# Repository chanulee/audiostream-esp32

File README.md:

# audiostream-esp32 — LOVELACE

AUX 스피커(3.5mm 라인 입력)에 꽂는 무선 오디오 수신기입니다. 한 개의 ESP32로 **AirPlay 2 · Spotify Connect · Bluetooth A2DP**를 모두 받고, 마지막으로 재생을 요청한 휴대폰이 출력을 가져갑니다.

| 항목 | 내용 |
|---|---|
| MCU | ESP32-WROVER-E-N8R8 (Flash 8MB, PSRAM 8MB, Wi-Fi + Bluetooth Classic) |
| DAC | PCM5102A, 3.5mm stereo line-out (2.1 Vrms) |
| 전원 | USB-C 5V → eFuse(OVP 5.8V, 전류 제한) → 3.3V buck / 저잡음 아날로그 LDO. 전원 스위치 없이 꽂으면 켜짐 |
| 보드 | LOVELACE / AS-008 rev A, 37 × 41mm 4층. USB-C와 AUX가 같은 변, 버튼 1개 |
| 수신 | AirPlay 2 (AAC/ALAC), Spotify Connect (cspot, Ogg Vorbis 320kbps), Bluetooth A2DP SBC + AVRCP |

S3 기반 이전 시제품(AS-001)은 Bluetooth Classic이 없어 A2DP를 받을 수 없으므로 WROVER로 전환했습니다. 첫 시제품부터 현재까지의 기록은 [hardware/archive](hardware/archive/README.md)에 있습니다.

## 빌드와 플래시

빌드용 Python은 3.11을 사용합니다. ESP-IDF 일부 의존성이 Python 3.14와 호환되지 않습니다.

```sh
python3.11 -m venv .venv
.venv/bin/pip install platformio==6.2.0
export PLATFORMIO_CORE_DIR="$PWD/work/platformio"
.venv/bin/pio run -d firmware -e lovelace-as-004 -t upload
.venv/bin/pio run -d firmware -e lovelace-as-004 -t uploadfs
.venv/bin/pio device monitor -b 115200
```

AS-003 이후 보드의 CH340N에는 DTR이 없어 자동 다운로드 모드 진입을 지원하지 않습니다. 업로드 전에 **버튼을 누른 채 USB를 꽂으세요.** 이후 펌웨어 업데이트는 웹 UI의 OTA로도 가능합니다.

버튼: 짧게 = 재생/일시정지, 두 번 = 다음 곡, 3초 = Bluetooth 페어링(연결된 폰을 끊고 새 폰 연결 대기).

| 환경 | 용도 |
|---|---|
| `lovelace-as-004` | 기본 펌웨어. AirPlay + Spotify + Bluetooth |
| `lovelace-as-004-capture` | 위 기능 + PCM 캡처 API (개발용, PSRAM 사용) |

## 첫 설정

1. 첫 부팅 시 `LOVELACE-Setup` Wi-Fi에 연결하고 `http://192.168.4.1/`에서 집의 2.4GHz Wi-Fi를 설정합니다.
2. Spotify: `http://<보드 IP>/spotify`에서 본인의 개발자 앱 Client ID / Secret을 입력하고 재부팅합니다. Premium 계정이 필요합니다. [설정 및 통합 설명](docs/SPOTIFY.md).
3. Bluetooth: 휴대폰의 Bluetooth 목록에서 `LOVELACE`를 선택합니다. 화면이 없으므로 Just Works 페어링을 사용하며, 구형 기기는 PIN `0000`을 사용합니다.

게스트 네트워크의 기기 격리나 mDNS 차단은 AirPlay·Spotify 검색을 방해합니다.

## 소스 전환 규칙

- 출력은 한 번에 하나의 소스만 사용합니다. 하나의 재생 태스크가 I2S를 쓰고, 소스는 `audio_source.c`의 출력 잠금 아래에서만 바뀝니다.
- **명시적 재생 요청이 출력을 가져옵니다.** AirPlay 재생, Spotify 재생/재개, Bluetooth AVRCP "playing" 보고가 해당합니다. 이전 소스는 일시정지 요청(Spotify yield, AVRCP pause)을 받고 대기 PCM은 버립니다.
- 다른 소스가 출력 중일 때 휴대폰 알림음이나 키보드 클릭처럼 A2DP 스트림만 열린 경우에는 출력을 가져오지 않습니다. 1.5초 이상 소리가 이어질 때만 재생으로 판단합니다.
- Bluetooth가 연결되어 있어도 AirPlay와 Spotify는 계속 검색됩니다. A2DP 48kHz 스트림은 I2S 클럭을 바꿔 리샘플링 없이 출력합니다.

## 테스트

```sh
sh tools/test_host.sh
```

호스트 테스트는 출력 소유권 전환(AirPlay/Spotify/Bluetooth), PCM FIFO 경계, 캡처 및 44.1/48kHz 전환, Spotify 연결 폼 파싱, WAV 저장을 확인합니다.

**검증 상태 (2026-10-16):** `lovelace-as-004` 펌웨어 0.3.1 빌드 성공, 호스트 테스트와 실크 편집기 테스트 전체 통과. **실기기 검증은 아직 없습니다.** 특히 Wi-Fi + Bluetooth + Spotify TLS를 동시에 켠 상태의 내부 RAM 여유, Wi-Fi/BT 공존 시의 끊김, 실제 계정의 Spotify 재생은 보드에서 측정해야 합니다.

### 캡처로 음질 확인

`lovelace-as-004-capture` 펌웨어에서 DAC 없이도 출력 PCM을 WAV로 받을 수 있습니다.

```sh
python3 tools/capture.py http://192.168.1.42 --seconds 3 -o capture.wav
```

[캡처 API](docs/CAPTURE_API.md)는 인증 없이 동작하므로 신뢰하는 로컬 네트워크에서만 사용하세요.

## 하드웨어

[LOVELACE / AS-008 rev A](hardware/lovelace-as-008/README.md)는 KiCad 10으로 스크립트 생성하며, [pcb-layout-skill](https://github.com/studio-edul/pcb-layout-skill)의 배치 검사기·계산기로 검증합니다. 제작 전 남은 항목은 [REVIEW.md](hardware/lovelace-as-008/REVIEW.md), 주문과 첫 보드 확인은 [BRINGUP.md](hardware/lovelace-as-008/BRINGUP.md)에 있습니다.

## 버전

| | 위치 | 버전 |
|---|---|---|
| 하드웨어 (현재) | `hardware/lovelace-as-008/` | AS-008 rev A (`plan_pcb.py`의 `BOARD_ID`, `BOARD_REV`) |
| 하드웨어 (이전) | `hardware/archive/NN-*/` | S3 rev A → AS-001 → AS-002 rev B → AS-002 rev C ([기록](hardware/archive/README.md)) |
| 펌웨어 | `firmware/version.txt` | 0.3.0 |

펌웨어 0.3.x는 AS-003부터 AS-008까지 전용입니다(AS-003–AS-006은 넷리스트가 같고, AS-007은 AUX 잭 단자 배정, AS-008은 USB via 크기와 eFuse ITIMER 미실장 패드만 다릅니다. 펌웨어와 무관합니다). 빌드 환경 이름은 `lovelace-as-004` 그대로 씁니다. DAC 뮤트(XSMT)를 GPIO22로 풀어야 소리가 나며, 0.2.x(ESP32-S3 / AS-001)는 이 보드들에서 동작하지 않습니다. 하드웨어 버전 규칙은 [archive/README.md](hardware/archive/README.md)에 있습니다.

## 문서

- [Spotify Connect 통합](docs/SPOTIFY.md)
- [연결 기능 조사: SDK, 다중 휴대폰, Bluetooth, Flash](docs/CONNECT_RESEARCH.md)
- [PCM 캡처 API](docs/CAPTURE_API.md)
- [기반 코드와 라이선스](docs/UPSTREAM.md). AirPlay 기반 코드는 비상업적 라이선스, cspot은 GPLv3입니다. 배포·판매 전에 권리 관계를 정리해야 합니다.

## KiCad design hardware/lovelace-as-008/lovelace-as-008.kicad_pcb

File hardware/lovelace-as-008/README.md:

# LOVELACE / AS-008 rev A

ESP32-WROVER-E-N8R8 + PCM5102A 일체형 수신 보드. **37 × 41 mm, 4층**, 단면 실장(JLCPCB Economic PCBA 가능). USB-C 전원과 3.5mm AUX가 아래 변에 있고, 모듈 안테나는 위 변 밖으로 나갑니다. 전원 스위치 없이 USB를 꽂으면 켜집니다.

렌더 전체(PCBA, 맨 기판, 부품 배치도, 층별 배선, 이전 빌드와의 차이, 버전 기록)는 `renders/latest/index.html`에 있습니다. 이전 버전은 [archive](../archive/README.md)에 있습니다. AS-002 rev C는 크기·부품 배치가 AS-003과 같고, AS-003에서 AUX 잭 배정, DAC 뮤트·홀드업, JLC 회전, 배선을 고쳤습니다. AS-004는 AS-003과 넷리스트·배치가 같습니다. 상단 SMD 패드에 닿던 via 10개를 없애도록 배선만 고쳤습니다([REVIEW_LAYOUT.md](REVIEW_LAYOUT.md)). AS-005는 AS-004와 넷리스트·배치·배선이 같고, AUX 잭(J2) 랜드만 Shou Han PJ-320D 도면대로 고쳤습니다(위치 결정 NPTH Ø1.0mm, 패드 폭 1.5mm; [archive/06](../archive/06-lovelace-as-004-revA/README.md)). AS-006은 J2 패드를 잭 축에서 도면 위치(3.85mm)로 옮기고, J2를 0.3mm 왼쪽으로 옮겨 다시 배선했습니다([archive/07](../archive/07-lovelace-as-005-revA/README.md)). AS-007은 LCSC 엔지니어 회신대로 J2 단자 배정을 고쳤습니다. AS-006까지는 오른쪽 채널과 GND가 바뀌어 있었습니다([archive/08](../archive/08-lovelace-as-006-revA/README.md)). AS-008은 회로·BOM이 AS-007과 같고, kicad-happy 검토([REVIEW_KICAD_HAPPY.md](REVIEW_KICAD_HAPPY.md))에 따라 USB D− via를 JLC 표준 크기로 키우고 eFuse ITIMER에 미실장 커패시터 자리를 더했습니다([archive/09](../archive/09-lovelace-as-007-revA/README.md)). 펌웨어도 그대로 호환됩니다.

| | AS-001 (S3) | AS-002 rev B | **AS-008 rev A (현재, AS-003과 회로 동일하고 AUX 잭 배선·USB via·ITIMER 랜드만 다름)** |
|---|---|---|---|
| 크기 | 55 × 55 mm (3,025 mm²) | 35 × 50 mm (1,750 mm²) | **37 × 41 mm (1,517 mm², −50%)** |
| 전원 | USB-C + 슬라이드 스위치 | USB-C + PCM12 스위치 | **USB-C, 꽂으면 켜짐** |
| 버튼 | BOOT + RESET (TL3342) | BOOT + RESET (B3U) | **버튼 1개 (B3U, GPIO0)** |
| AUX 잭 | CUI SJ1-3523N (THT) | 동일 | **PJ-320D (SMD, C431535, 제조사 도면 랜드)** |
| 버크 인덕터 / 출력 C | 4 × 4 mm / 47µF 1206 | 동일 | **2.0 × 1.6 mm / 22µF 0805** |
| 고정 홀 | M3 × 4 | M2 × 2 | **M2 × 1 (오른쪽 위, NPTH, 나일론 나사 권장)** |
| 배선 | — | 미완료 | **완료 (KiCadRoutingTools 3단계 + 손 배선 3개), DRC 0, 패드 안 via 0** |
| 테스트 패드 | — | — | **바닥면 11개 (전원 레일, UART, EN, IO0)** |

## 회로

```
USB-C VBUS ─ TPS25947 eFuse (UVLO 4.26V / OVLO 5.80V / ILIM ≈0.65A) ─ +5V
   ├ CC1/CC2 5.1k                 +5V ─ TPS62162 buck (2.2µH 2016) ─ +3V3_D (L3 평면, ESP32)
   └ D+/D− ─ USBLC6 ─ CH340N ─ UART0   +5V ─ RB551V ─ +5V_DAC (220µF 홀드업) ─ TPS7A2033 ─ +3V3_A
ESP32-WROVER-E  GPIO21 BCK / GPIO19 DIN / GPIO18 LRCK ─ PCM5102A (AVDD·CPVDD·DVDD = +3V3_A)
                GPIO22 ─ XSMT (10k 풀다운 = 기본 뮤트)    ─ 470Ω/2.2nF ─ ESD ─ PJ-320D
                GPIO23 LED, GPIO0 버튼(+10k 풀업), EN = 10k/1µF RC
```

| 신호 | ESP32 | 모듈 핀 |
|---|---|---|
| I2S BCK | GPIO21 | 33 |
| I2S DIN | GPIO19 | 31 |
| DAC 뮤트 (XSMT, low = 뮤트) | GPIO22 | 36 |
| I2S LRCK | GPIO18 | 30 |
| Status LED | GPIO23 | 37 |
| 버튼 / 다운로드 모드 | GPIO0 | 25 |
| UART0 RX / TX | RXD0 / TXD0 | 34 / 35 |

I2S 핀은 DAC의 핀 순서(BCK, DIN, LRCK)와 같은 순서로 모듈에서 나오도록 다시 배정해 교차가 없습니다. 펌웨어(`config/sdkconfig.defaults.lovelace-wrover`)가 같은 핀을 씁니다. 5mm 정도로 짧아 직렬 33Ω 저항은 없앴습니다(1ns 에지 기준 임계 길이 약 25mm).

**버튼:** 짧게 = 재생/일시정지, 두 번 = 다음 곡, 3초 = Bluetooth 페어링(연결된 폰을 끊고 새 폰을 받음). 버튼을 누른 채 USB를 꽂으면 ROM 다운로드 모드로 들어갑니다(CH340N에는 DTR이 없음).

**팝 대책.** XSMT는 10k 풀다운이라 리셋·부팅 동안 DAC가 뮤트돼 있습니다. 펌웨어는 I2S 클럭이 20ms 돈 뒤 GPIO22로 뮤트를 풀고, 샘플레이트 변경·flush·`esp_restart` 전에는 다시 뮤트한 뒤 소프트 뮤트 램프(5ms)를 기다립니다. USB를 갑자기 뽑으면 D5/C25가 DAC 전원을 홀드업합니다. 16개 동작 모델 조건에서 ESP32 브라운아웃(클럭 정지 가정) 후 공통 DAC 전원 3.1V까지 최소 3.441ms로, clock-stop 기준 3ms를 넘었습니다. 이는 저항성 부하·이상적인 버크·고정 LDO 강하를 쓴 모델 결과이며 실측 전입니다. XSMT 경로는 별도의 150 샘플 + 0.2ms 기준으로 다룹니다([새 검증 결과](VALIDATION_RESULTS.md)).

PJ-320D는 4극(TRRS) 잭입니다. 풋프린트(`LOVELACE:Jack_3.5mm_PJ320D_Horizontal_ShouHan`)는 Shou Han 도면을 따릅니다. 위치 결정 홀 Ø1.0mm(핀 Ø0.75mm), 플러그 축 방향 패드 폭 1.5mm, 축 방향 패드 위치는 KiCad `Connector_Audio:Jack_3.5mm_PJ320D_Horizontal`과 같습니다(도면과 0.1mm 이내). 축에서 패드까지는 도면대로 몸체(폭 6.1mm) 바깥 3.05–4.65mm에 랜드를 두되, 양 끝을 0.2mm씩 늘려 2.85–4.85mm(길이 2.0mm)로 했습니다. KiCad 풋프린트는 2.0–4.5mm라 1mm가 몸체 아래로 들어가고 단자 끝을 덮지 못했습니다. `cpl.csv`의 J2 좌표는 패드 평균이 아니라 위치 결정 핀 기준입니다(JLC 핀과 우리 홀 차이 0.000mm). 도면은 단자를 개구부 쪽부터 D, C, B, A로 표시하고(KiCad `R2`, `R1`, `T`, `S`), 기능은 적지 않았습니다. LCSC 엔지니어 회신(2026-10-16)과 도면 회로도 기준으로 A = Tip, D = Ring 1, C = Ring 2, B = Sleeve입니다. 단자 위치는 접점이 플러그에 닿는 위치와 다릅니다. 배정은 A(`S`) = LINE_L, D(`R2`, 개구부 쪽) = LINE_R, B(`T`)와 C(`R1`) = GND입니다. 일반 3극 플러그의 긴 슬리브가 B와 C를 함께 잇습니다. `audit_pcb.py`와 `pinout_check.py`가 이름 대신 개구부에서의 거리 순서로 이 배정을 검사합니다.

고정 홀 H1(M2, 2.2mm NPTH)은 오른쪽 위에 있고, 지름 5.5mm 안에는 구리가 없습니다. 안테나 끝에서 약 11mm 떨어져 있으므로 금속 대신 나일론 나사·스페이서를 권장합니다.

## 층 구성

L1 부품 + 신호 + GND pour, **L2 GND 전면**, L3 +3V3_D 전면, L4 신호 + GND pour. +3V3_A(약 30mA)는 LDO에서 DAC로 배선합니다.

## 생성

### 렌더링 도구

렌더링 코드, 뷰어, 의존성, 테스트는 [`rendering/`](rendering/README.md)에 있습니다. `make_board.sh`는 `rendering/render_board.py`를 부릅니다.

```sh
bash rendering/run.sh                        # STEP 기반 인터랙티브 뷰어 (http://127.0.0.1:8877)
./rendering/render_extra.sh                  # renders/extra/: KiCad 3D 다각도 뷰, 층별 SVG/PDF
```

### 실크 인쇄 편집기

repo 루트에서 `python3 tools/silkscreen_editor.py`를 실행하고 출력된 전체 로컬 URL을 엽니다.
KiCad 10의 Python과 CLI를 자동으로 사용하며, 별도 패키지 설치는 필요 없습니다.
KiCad를 다른 위치에 설치했다면 `KICAD`를 해당 앱의 `Contents` 경로로 지정합니다.

- 앞·뒷면에서 SVG와 텍스트를 배치하고, 드래그 또는 mm 좌표·크기·회전 입력으로 조정합니다.
- 좌표는 선택한 면의 왼쪽 위 기준입니다. 뒷면을 밖에서 읽는 방향으로 편집하며, PCB 좌표와 미러 처리는 자동입니다.
- SVG의 불투명 영역은 단색 실크로 변환합니다. 흰 배경이 있으면 `흰 배경 제외`를 선택합니다. SVG 내 외부 이미지·실행 코드·애니메이션은 지원하지 않습니다.
- SVG는 0.025 mm 간격으로 샘플링한 뒤 채워진 KiCad 도형으로 저장합니다. 복잡한 곡선은 근사되며 원본 SVG도 편집 파일에 보관됩니다. 텍스트 미리보기 글꼴은 실제 KiCad 글꼴과 다릅니다.
- 구리 배선·패드 표시를 켜면 현재 면의 배선과 보드 경계선을 함께 봅니다(구리 평면은 생략). 마스크로 덮인 배선 위 실크는 허용됩니다.
- `실제 인쇄·간섭 검사`는 저장 전 배치를 임시 PCB에 적용해 KiCad 실제 글꼴로 렌더하고, 현재 면의 실크 간섭을 빨간 상자·번호로 표시합니다. 원본 PCB는 바꾸지 않습니다. `편집 계속`으로 돌아가 수정한 뒤 다시 검사하세요. 전체 제작 검사는 `make_board.sh`로 수행합니다.
- `PCB에 저장`은 현재 보드 파일(`lovelace-as-008.kicad_pcb`)과 `silkscreen.json`을 업데이트합니다. 편집기는 `hardware/versions.json`에서 현재 보드를 찾고, 화면에 보드 ID와 rev를 표시합니다. 기존 board-level 실크를 편집기가 관리하며, footprint의 실크·구리 배선·부품 배치는 유지합니다.
- 저장 전 PCB는 `.silk-backup.kicad_pcb`, 이전 배치는 `silkscreen.json.bak`으로 1회분 백업합니다. 다른 프로그램이 파일을 수정했으면 저장을 거부합니다. 저장할 때 KiCad 프로젝트를 닫으세요.
- `make_board.sh`로 재생성해도 `silkscreen.json`이 적용됩니다. 편집기 저장만으로 Gerber·release ZIP이 갱신되지는 않습니다. 제작 전 아래 생성 명령과 DRC로 패드·가장자리 간섭을 확인하세요.

검증: `node tests/test_silkscreen_mask.js`; KiCad Python으로 `-m unittest discover -s tests -p test_silkscreen.py -v`.

```sh
./make_board.sh               # 재생성 + JLC 대조 + 배선 + 검사 + release zip + 렌더
RENDER=0 ./make_board.sh      # 렌더 생략
./make_board.sh anneal 3      # 수동 부품 배치를 다시 탐색(seed 3)
ROUTER=freerouting REROUTE=1 ./make_board.sh   # 비교용: FreeRouting으로 배선
```

| 스크립트 | 역할 |
|---|---|
| `plan_pcb.py` | 넷리스트, 큰 부품과 DAC 주변의 수동 배치, 검사 규칙, LCSC 부품 번호 |
| `autoplace.py` | 나머지 수동 부품을 스킬 검사기 규칙(간격, 가장자리, keep-out, near/apart)과 핀 단위 배선 길이를 비용으로 annealing |
| `build_pcb.py` | 보드·회로도·BOM·CPL·DSN 생성, 직접 그린 배선(버크 SW, USB D+/D−, VBUS, 평면 via), 고정 UUID |
| `jlc_check.py` | JLC/EasyEDA 부품 데이터와 패드·극성 대조, JLC 기준 회전·원점으로 `cpl.csv` 작성, 재고와 Basic/Extended 보고(`reports/jlc.json`) |
| `finish_pcb.py` | (FreeRouting이면 .ses 가져오기) KiCad 연결성 기준으로 쓰지 않은 via 정리, 바닥 테스트 패드, 평면 채우기 |
| `rendering/render_board.py` | 3D PCBA·맨 기판, 부품 배치도, 층별 구리, 넷 종류별 배선도, 이전 빌드와의 차이, `index.html` |
| `pinout_check.py` | 데이터시트 핀·수동부품의 값/넷/실장 상태 계약 305개 대조( [REVIEW_NETLIST.md](REVIEW_NETLIST.md)) |
| `sim/power_path.py` | ngspice 전원 경로 동작 모델: 완주/측정값 확인, eFuse 기동, ESP32 펄스 부하, 16조건 C25 홀드업(3.1V/clock-stop 기준)([REVIEW_NETLIST.md](REVIEW_NETLIST.md) 4절) |
| `rendering/render_extra.sh` | `renders/extra/`: 3D 뷰(6면 + 6각도), 층별 SVG, 전체 층 PDF, 보드 SVG, 회로도 PDF (`QUALITY=basic`이면 빠름). U1·J1·J2는 KiCad에 3D 모델이 없어 LCSC/EasyEDA STEP(`lib/3d/`)을 씁니다 |
| `audit_pcb.py` | 좌표·핀넷 readback, 디커플링 패드 거리, 라이브러리와 패드 형상 비교, AUX 잭 접점 순서 |

전원 검사에는 PATH에 `ngspice`가 필요합니다.

필요한 것: KiCad 10(`/Volumes/KiCad` 마운트)과 `work/tools/` 아래 세 가지입니다. [pcb-layout-skill](https://github.com/studio-edul/pcb-layout-skill) 체크아웃(`pcb-layout-skill/`, 다른 위치면 `SKILL`로 지정), [KiCadRoutingTools](https://github.com/drandyhaas/KiCadRoutingTools) v0.23.0(`krt/`), 그리고 numpy·scipy·shapely를 설치한 venv(`krt-venv/`)입니다. 설치 후 `krt-venv/bin/python krt/build_router.py`로 라우터 바이너리를 받습니다. FreeRouting 비교에는 FreeRouting 2.5.0과 Java 25 런타임이 더 필요합니다.

배선은 KiCadRoutingTools를 씁니다. 같은 배치에서 FreeRouting과 비교한 결과입니다(둘 다 DRC 0).

| | FreeRouting | KiCadRoutingTools (현재) |
|---|---:|---:|
| 신호 배선 길이 / 세그먼트 | 442mm / 371 | 403mm / 239 |
| 0.2mm 미만 세그먼트 | 53 | 9 |
| 전원 0.225mm 넥다운 | VBUS·+5V·+5V_DAC·+3V3_A 14mm | 없음 (0.25mm 손 배선 2mm만) |
| 오디오 넷의 B.Cu(디지털 전원 평면 위) 구간 | DAC_L/R, LINE_L via 6개 | 없음 |
| 아날로그–잡음선 최소 간격(같은 층) | 0.37mm | 1.14mm |
| 신호 via | 35 | 32 |
| 재현성 | 실행마다 다름 | 항상 같음 |

KiCadRoutingTools는 3단계로 배선합니다. ① 오디오 넷(DAC_L/R, LINE_L/R, VNEG, CAPP/CAPM, LDOO)을 F.Cu에만, ② 전원(VBUS, +5V, +5V_DAC, +3V3_A, SW)을 0.3mm 고정으로(축소 금지), ③ 나머지를 0.2mm로(자리가 없으면 보드 최소값 0.15mm까지) 배선합니다. +5V_DAC의 C25 → D5 구간은 `build_pcb.py`가 오른쪽 가장자리로 직접 그립니다. 라우터에 맡기면 I2S 세 선을 가로질러 I2S가 바닥층으로 넘어갔기 때문입니다. eFuse의 OVLO·ILIM(2 × 2mm QFN 가운데 핀)도 `build_pcb.py`가 그립니다. via를 패드에서 띄우면 라우터가 빠져나갈 길을 찾지 못하기 때문입니다. via를 놓는 ②③단계는 `--same-net-pad-clearance 0.1`로 via를 같은 넷 SMD 패드에서 0.1mm 이상 띄웁니다. 메우지 않은 via가 패드 안에 있으면 리플로 때 땜납이 빠져나가기 때문입니다. ①이 끝나면 오디오 배선을 잠가서, ②③이 막혔을 때 이를 뜯어 B.Cu로 옮기지 못하게 합니다. `audit_pcb.py`는 상단 SMD 패드에 닿는 via가 있으면 실패합니다. 보드 항목 UUID를 고정해 같은 설계는 항상 같은 배선이 나옵니다.

## 상태 (2026-10-19, AS-008)

- 배치 검사 ERROR 0 / WARN 0, 점유율 76%. 데이터시트 핀 대조 142/142(J2 포함).
- KiCad DRC 0, 미연결 0, 회로도 parity 0, ERC 0(위반이 있으면 `make_board.sh`가 릴리스 전에 멈춤). 디커플링 패드 거리 19/19, 라이브러리 패드 일치 55/55, JLC 부품 데이터 대조 53/53(C26은 미실장이라 제외).
- 릴리스 감사 0/0(BOM·CPL 포함), Gerber netcheck shorts 0 / opens 0. `lovelace-as-008-revA-release.zip`에 Gerber, drill, IPC-D-356, JLC 형식 BOM / CPL.
- AS-006 대비: J2 넷 배정(D = LINE_R, B = GND), ESD 다이오드 D2 위치(24.5, 30.0 → 25.0, 33.9mm), 그에 따른 재배선(세그먼트 328, via 96, 길이 496 → 501mm, LINE_R 24.4 → 29.2mm, 오디오 넷 B.Cu 0·via 0). 같은 층에서 LINE_R과 버크 SW 넷의 최소 간격은 4.18mm입니다(AS-006은 5.6mm 이상). LINE_R은 R12 470Ω 뒤 저임피던스 선이고 바로 아래가 L2 GND 평면이라 문제로 보지 않지만, 첫 보드에서 오른쪽 채널 잡음을 왼쪽과 비교해 확인합니다. J2 랜드와 BOM은 같고, CPL은 D2 한 줄만 바뀌었습니다.
- AS-007 대비: USB_DM via 4개 0.4/0.2 → 0.45/0.2mm(JLC 다층 표준 최소 지름 0.45mm, 이제 0.45mm 미만 via 없음; 넷 클래스와 보드 최소값도 0.45mm). U6 ITIMER(10번)에 미실장 0402 C26(ITIMER–GND)을 두고 2mm로 직접 연결했습니다. C26 패드는 구리와 마스크 개구부만 있고 솔더 페이스트는 없습니다(KiCad DNP 표시만으로는 페이스트 Gerber에서 빠지지 않아 `build_pcb.py`가 F.Paste 층을 뺌). TPS259470A는 전류를 끊는 차단형이 아니라 전류 제한형입니다. 부하가 ILIM을 넘으면 출력 전류를 ILIM으로 묶고, 이 상태가 길어져 과열되면 꺼졌다가 110ms 뒤 다시 켜집니다. C26을 비워 두면 ILIM을 넘는 즉시 제한이 걸립니다(데이터시트상 가장 빠른 응답). 첫 보드에서 Wi-Fi 피크가 이 제한에 걸려 3.3V가 처지면 C26에 1–10nF를 답니다. 그러면 ILIM과 2 × ILIM 사이의 짧은 피크가 nF당 약 0.8ms 동안 제한 없이 통과합니다. 2 × ILIM을 넘는 전류는 C26과 상관없이 빠르게 제한됩니다. C26 자리는 R16이 있던 곳이고, R16은 U6 EN/UVLO(1번) 옆(11.7, 35.88mm)으로 옮겨 POWER_EN 배선이 13.3 → 6.1mm로 줄었습니다. 바뀐 배선은 VBUS·+5V·GND·POWER_EN·ITIMER뿐이고(세그먼트 330, via 98, 길이 495mm), 오디오 넷은 그대로입니다(F.Cu만, via 0, LINE_R 29.2mm). BOM은 같고, CPL은 R16 한 줄만 바뀌었습니다.
- 제작 전 확인할 항목은 [REVIEW.md](REVIEW.md), 주문과 첫 보드 확인 절차는 [BRINGUP.md](BRINGUP.md)에 있습니다.

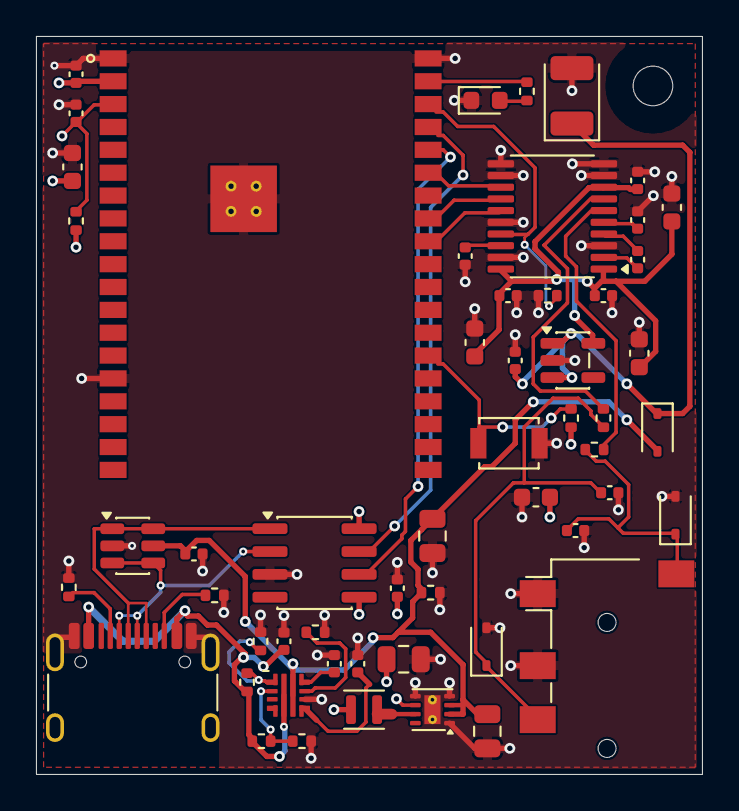
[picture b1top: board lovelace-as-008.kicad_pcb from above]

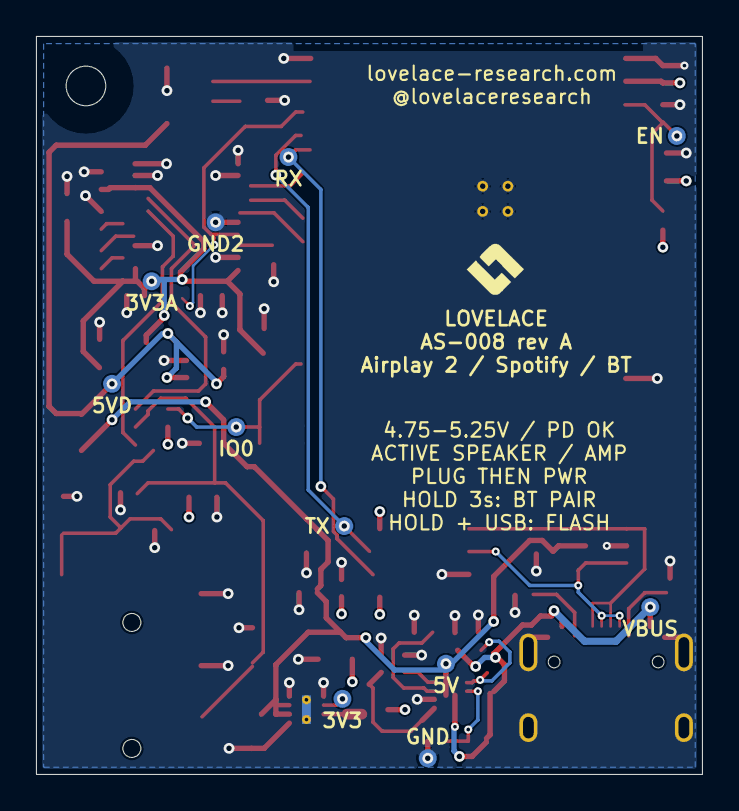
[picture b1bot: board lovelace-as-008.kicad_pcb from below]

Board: 4 copper layers, 37.0 x 41.0 mm, 66 parts (11 on the bottom side), 34 nets.

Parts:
3V3: +3V3_D; TestPoint_Pad_D1.0mm
3V3A: +3V3_A; TestPoint_Pad_D1.0mm
5V: +5V; TestPoint_Pad_D1.0mm
5VD: +5V_DAC; TestPoint_Pad_D1.0mm
C1, C8: 1uF; C_0402_1005Metric
C2, C10, C14, C16, C18, C21, C23, C24: 100nF; C_0402_1005Metric
C3, C5, C9, C15, C17: 10uF; C_0603_1608Metric
C4, C7: 10uF; C_0805_2012Metric
C6: 22uF; C_0805_2012Metric
C12, C13: 2.2uF; C_0402_1005Metric
C19, C20: 2.2nF; C_0402_1005Metric
C22: 10nF; C_0402_1005Metric
C25: 220uF; CP_EIA-3528-21_Kemet-B
C26: DNP; C_0402_1005Metric
D2, D3: PESD5V0S1BA; D_SOD-323
D4: KT-0603G; LED_0603_1608Metric
D5: RB551V-30; D_SOD-323
EN: EN; TestPoint_Pad_D1.0mm
GND, GND2: GND; TestPoint_Pad_D1.0mm
H1: M2; MountingHole_2.2mm_M2
IO0: BOOT; TestPoint_Pad_D1.0mm
J1: HRO TYPE-C-31-M-12; USB_C_Receptacle_HRO_TYPE-C-31-M-12
J2: PJ-320D; Jack_3.5mm_PJ320D_Horizontal_ShouHan
L1: 2.2uH; L_Murata_DFE201610P
R1, R2, R15: 5.1k; R_0402_1005Metric
R5, R6, R10: 10k; R_0402_1005Metric
R11, R12: 470; R_0402_1005Metric
R13: 383k; R_0402_1005Metric
R14, R17, R19: 100k; R_0402_1005Metric
R16: 255k; R_0402_1005Metric
R18: 220; R_0402_1005Metric
RX: UART_RX; TestPoint_Pad_D1.0mm
SW1: B3U-1000P; SW_SPST_B3U-1000P
TX: UART_TX; TestPoint_Pad_D1.0mm
U1: ESP32-WROVER-E-N8R8; ESP32-WROVER-E
U2: PCM5102APWR; TSSOP-20_4.4x6.5mm_P0.65mm
U3: TPS62162DSGR; Texas_DSG0008A_WSON-8-1EP_2x2mm_P0.5mm_EP0.9x1.6mm_ThermalV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
U4: TPS7A2033PDBVR; SOT-23-5
U5: USBLC6-2SC6; SOT-23-6
U6: TPS259470ARPWR; TPS25947_RPW0010A
U7: CH340N; SOIC-8_3.9x4.9mm_P1.27mm
VBUS: VBUS; TestPoint_Pad_D1.0mm

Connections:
+3V3_A: 3V3A.1, C9.1, C10.1, C14.1, C15.1, C16.1, C17.1, U2.1, U2.8, U2.20, U4.5
+3V3_D: 3V3.1, C2.1, C3.1, C5.1, C6.1, C24.1, L1.2, R5.1, R6.1, U1.2, U3.6, U7.5, U7.8
+5V: 5V.1, C4.1, C7.1, C23.1, D5.2, R19.1, U3.2, U3.3, U5.5, U6.6
+5V_DAC: 5VD.1, C8.1, C25.1, D5.1, U4.1, U4.3
BCLK: U1.33, U2.13
BOOT: IO0.1, R6.2, SW1.1, U1.25
CAPM: C12.2, U2.4
CAPP: C12.1, U2.2
CC1: J1.A5, R1.1
CC2: J1.B5, R2.1
DAC_L: R11.1, U2.6
DAC_R: R12.1, U2.7
DATA: U1.31, U2.14
DVDT: C22.1, U6.7
EN: C1.1, EN.1, R5.2, U1.3
GND: C1.2, C2.2, C3.2, C4.2, C5.2, C6.2, C7.2, C8.2, C9.2, C10.2, C13.2, C14.2, C15.2, C16.2, C17.2, C18.2, C19.2, C20.2, C21.2, C22.2, C23.2, C24.2, C25.2, C26.2, D2.2, D3.2, D4.1, GND.1, GND2.1, J1.A1, J1.A12, J1.B1, J1.B12, J1.SH, J2.R1, J2.T, R1.2, R2.2, R10.1, R14.2, R15.2, R17.2, R19.2, SW1.2, U1.1, U1.15, U1.38, U1.39, U2.3, U2.9, U2.10, U2.11, U2.12, U2.16, U2.19, U3.1, U3.4, U3.5, U3.9, U4.2, U5.2, U6.8, U7.3
ILIM: R15.1, U6.9
ITIMER: C26.1, U6.10
LDOO: C18.1, U2.18
LINE_L: C19.1, D3.1, J2.S, R11.2
LINE_R: C20.1, D2.1, J2.R2, R12.2
LRCLK: U1.30, U2.15
OVLO: R13.2, R14.1, U6.2
POWER_EN: R16.2, R17.1, U6.1
STATUS_A: D4.2, R18.2
STATUS_GPIO: R18.1, U1.37
SW: L1.1, U3.7
UART_RX: RX.1, U1.34, U7.6
UART_TX: TX.1, U1.35, U7.7
USB_DM: J1.A7, J1.B7, U5.3, U5.4, U7.2
USB_DP: J1.A6, J1.B6, U5.1, U5.6, U7.1
VBUS: C21.1, J1.A4, J1.A9, J1.B4, J1.B9, R13.1, R16.1, U6.5, VBUS.1
VNEG: C13.1, U2.5
XSMT: R10.2, U1.36, U2.17

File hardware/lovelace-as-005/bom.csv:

Comment,Designator,Footprint,LCSC Part #,Quantity
1uF,"C1,C8",C_0402_1005Metric,C52923,2
2.2uF,"C13,C12",C_0402_1005Metric,C12530,2
2.2nF,"C19,C20",C_0402_1005Metric,C106861,2
100nF,"C2,C18,C14,C10,C16,C23,C24",C_0402_1005Metric,C1525,7
100nF,C21,C_0402_1005Metric,C307331,1
10nF,C22,C_0402_1005Metric,C15195,1
220uF,C25,CP_EIA-3528-21_Kemet-B,C212684,1
10uF,"C3,C15,C17,C9,C5",C_0603_1608Metric,C19702,5
22uF,C6,C_0805_2012Metric,C45783,1
10uF,"C7,C4",C_0805_2012Metric,C15850,2
PESD5V0S1BA,"D2,D3",D_SOD-323,C19224,2
KT-0603G,D4,LED_0603_1608Metric,C12624,1
RB551V-30,D5,D_SOD-323,C8529,1
HRO TYPE-C-31-M-12,J1,USB_C_Receptacle_HRO_TYPE-C-31-M-12,C165948,1
PJ-320D,J2,Jack_3.5mm_PJ320D_Horizontal_ShouHan,C431535,1
2.2uH,L1,L_Murata_DFE201610P,C79317,1
5.1k,"R1,R2,R15",R_0402_1005Metric,C25905,3
470,"R11,R12",R_0402_1005Metric,C25117,2
383k,R13,R_0402_1005Metric,C163468,1
100k,R14,R_0402_1005Metric,C852472,1
255k,R16,R_0402_1005Metric,C270623,1
220,R18,R_0402_1005Metric,C25091,1
100k,"R19,R17",R_0402_1005Metric,C25741,2
10k,"R5,R10,R6",R_0402_1005Metric,C25744,3
B3U-1000P,SW1,SW_SPST_B3U-1000P,C231329,1
ESP32-WROVER-E-N8R8,U1,ESP32-WROVER-E,C2973667,1
PCM5102APWR,U2,TSSOP-20_4.4x6.5mm_P0.65mm,C107671,1
TPS62162DSGR,U3,Texas_DSG0008A_WSON-8-1EP_2x2mm_P0.5mm_EP0.9x1.6mm_ThermalVias,C40256,1
TPS7A2033PDBVR,U4,SOT-23-5,C2862740,1
USBLC6-2SC6,U5,SOT-23-6,C7519,1
TPS259470ARPWR,U6,TPS25947_RPW0010A,C3662799,1
CH340N,U7,SOIC-8_3.9x4.9mm_P1.27mm,C2977777,1

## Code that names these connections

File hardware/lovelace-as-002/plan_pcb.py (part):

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part('U1', 'ESP32-WROVER-E-N8R8', 'LOVELACE:ESP32-WROVER-E', 13.01, U1_Y, 0,
     {1: 'GND', 2: '+3V3_D', 3: 'EN', 15: 'GND', 25: 'BOOT', 30: 'LRCLK',
      31: 'DATA', 33: 'BCLK', 34: 'UART_RX', 35: 'UART_TX', 36: 'XSMT',
      37: 'STATUS_GPIO', 38: 'GND', 39: 'GND'},
     names={str(i + 1): n for i, n in enumerate(module_names)}, kind='module')
# Left strip: 3V3 100 nF at pin 2, bulk, EN RC.
C('C2', '100nF', 2.2, 2.1, '+3V3_D', rot=90)
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# No I2S series resistors: module-to-DAC traces are ~5 mm, far below the
# ~25 mm critical length of a 1 ns edge.
C('C18', '100nF', 23.82, 12.2, 'LDOO', rot=270)
# Right pin row: AVDD, VNEG, charge-pump flying cap; CPVDD below pin 1. The
# AVDD 10 uF stands right of that column so the top-right corner is free for H1.
C('C15', '10uF', 35.3, 9.5, '+3V3_A', rot=90, mid=True)
C('C14', '100nF', 33.4, 8.0, '+3V3_A', rot=90)
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C('C12', '2.2uF', 33.4, 12.4, 'CAPP', 'CAPM', rot=90)
C('C10', '100nF', 31.5, 14.4, '+3V3_A')
C('C16', '100nF', 26.2, 14.4, '+3V3_A')
# XSMT pull-down: the DAC stays muted through reset and boot until GPIO22
# drives it high.
R('R10', '10k', 28.4, 14.4, 'GND', 'XSMT')
C('C17', '10uF', 24.35, 17.0, '+3V3_A', rot=90, mid=True)
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# --- Status / buttons -------------------------------------------------------
part('D4', 'KT-0603G', 'LED_SMD:LED_0603_1608Metric', 28.6, 1.5, 0,
     {1: 'GND', 2: 'STATUS_A'}, names={'1': 'K', '2': 'A'})
R('R18', '220', 25.6, 1.5, 'STATUS_GPIO', 'STATUS_A')   # green Vf ~2.9 V at 3.3 V
# One user button on GPIO0: playback / pairing at runtime; held while USB is
# plugged in it selects the ROM download mode (CH340N has no DTR).
part('SW1', 'B3U-1000P', 'Button_Switch_SMD:SW_SPST_B3U-1000P', 26.25, 22.6, 0,
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    ('C14', 'U2', 1.0, 'B1 AVDD 100 nF'), ('C10', 'U2', 1.0, 'B1 CPVDD 100 nF'),
    ('C16', 'U2', 1.0, 'B1 DVDD 100 nF'), ('C18', 'U2', 1.0, 'B1 LDOO 100 nF'),
    ('C12', 'U2', 1.0, 'charge-pump flying cap at pins 2/4'),
    ('C13', 'U2', 1.0, 'VNEG cap at pin 5'),
    ('C9', 'U2', 5.0, 'B1 CPVDD / AVDD 10 uF'), ('C15', 'U2', 5.0, 'B1 10 uF'),
    ('C17', 'U2', 5.0, 'B1 10 uF'),
    ('C8', 'U4', 3.0, 'B1 LDO input'), ('C9', 'U4', 3.0, 'B1 LDO output'),
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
